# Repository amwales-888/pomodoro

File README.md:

# Pomodoro Timer

This simple project was requested by a client.

### Step 1. Hardware time preset

Produce a Pomodoro Timer where you can set the working time and rest time

The client proposed a set of jumper headers to configure timers along with a sketch of the hardware.

<table>
  <tr>
    <td> </td>
    <td> </td>
  </tr>
</table>

Timers value are hardcoded 

Working time

- 15 minutes
- 30 minutes
- 60 minutes
- 90 minutes

Relax time

-  0 min
-  5 min
- 10 min
- 15 min

A row of LED are used to display the state of the timers.

### Step 2. Start timer

User clicks button to start timer

User hears sound from buzzer

LED progress bar turned on 

- Logic of the LED progress bar
    - Countdown progress bar
        - Ex: 30 minutes timer
        - 10 LEDs are on
        - the last one 10th is flashing
        - Every 3 minutes (time/amount of leds) 1 led turn off, after 3 minutes only 9 are on, the 9th is flashing

### Step 3. Timer is over

Once working timer is over:

- All progress bar LEDs flash
- Buzzer produce sound

Then User click button and Relax(Rest) timer began with the same logic

- Led progress bar has different color
- Once Rest timer finished - another melody is playing

To stop timer the User must hold the button pressed for 3 seconds. 

No pause function needed

### Power requirements

Ideally make it run from a tiny battery like CR2032 or 2-3 AAA Batteries.

### Enclosure requirements

No enclosure or enclosure built from PCB

### Size requirements

Less than 85 mm x 50mm 

## Proposal

 - Use a lowcost <a href="Firmware/pic16f15355/docs/PIC16F-LF-15354-55-Data-Sheet-DS40001853.pdf">pic16lf15355</a> SOIC 28 MCU which can be powered from 1.8v-5v, running from internal oscillator and able to idle at very low current.
 - Use 7 red/green bi-color, low power LEDs 
 - Use 2 AAA Batteries in series at 2v-3v to extend runtime and reduce end user cost over lithium CR2032 cell.
 - Use Microchip MPLAB-X, XC8 and Pickit5 for development.
 - 67mm x 40mm board area, battery holder mounted on the back.

<table>
  <tr>
    <td> </td>
    <td> </td>
  </tr>
</table>

## Completed Project 

Working, partially populated board 

## Project revision

I recently started investigating the py32 series of microcontrollers from puya, these are very low cost ( 12cents, you read that correctly ) arm-cortex-m0 processors running at 24MHz.
I ported the pomodoro firmware for the pic16 targeting the py32 controller and redsigned the board to support a tssop20 package. The new hardware is aimed at owering costs, along with the processor selection I opted for 14 leds in 0603 packages to reduce the cost. The complete BOM comes in at less than $1 and has feature parity with the original, supporting the same number of output and inputs as the original.

<table>
  <tr>
    <td> </td>
    <td> </td>
  </tr>
</table>

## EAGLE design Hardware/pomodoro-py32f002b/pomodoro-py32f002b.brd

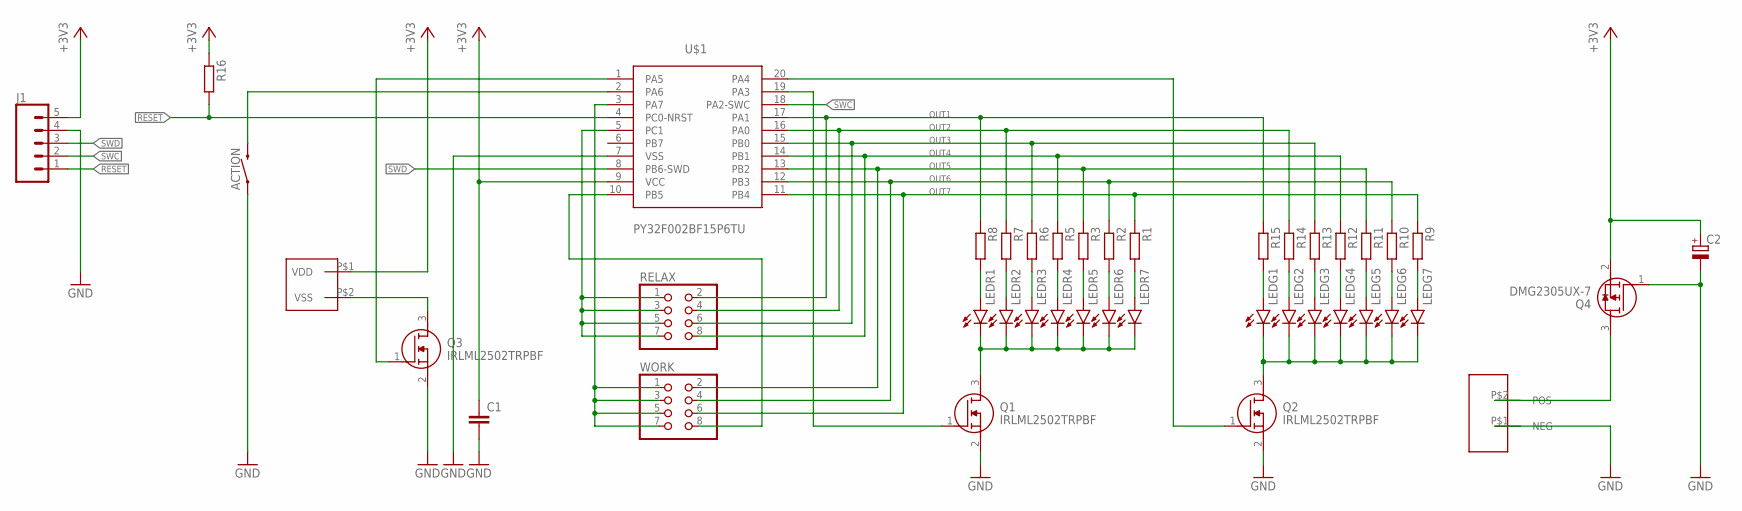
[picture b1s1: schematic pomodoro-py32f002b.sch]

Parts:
ACTION: MOMENTARY-SWITCH-SPST-SMD-6.0X3.5MM; TACTILE_SWITCH_SMD_6.0X3.5MM
C1: C-EUC0805; C0805
C2: CPOL-EUE2.5-5; E2,5-5
J1: CONN_05; 1X05
LEDG1, LEDG2, LEDG3, LEDG4, LEDG5, LEDG6, LEDG7: 20ma; SML0805
LEDR1, LEDR2, LEDR3, LEDR4, LEDR5, LEDR6, LEDR7: 20ma; SML0805
Q1, Q2, Q3: IRLML2502TRPBF; SOT95P237X112-3N
Q4: DMG2305UX-7; SOT96P240X115-3N
R1, R2, R3, R5, R6, R7, R8, R9, R10, R11, R12, R13, R14, R15, R16: 100R; R0805
RELAX: PINHD-2X4; 2X04
U$1: PY32F002BF15P6TU; TSSOP20
U$2: BUZZER8X8
U$3: 2AAABATT; 2AAABATTSER
WORK: PINHD-2X4; 2X04

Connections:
+3V3: C1.1, C2.+, J1.5, Q4.2 (S), R16.1, U$1.9 (VCC), U$2.P$1 (VDD)
BIN: Q1.1 (G), U$1.19 (PA3); also elsewhere on the board
BIN1: Q2.1 (G), U$1.20 (PA4); also elsewhere on the board
GND: ACTION.1, C1.2, C2.-, J1.4, Q1.2 (S), Q2.2 (S), Q3.2 (S), Q4.1 (G), U$1.7 (VSS), U$3.P$1 (NEG); also elsewhere on the board
LEDR1: LEDR1.A, R8.2
unnamed: LEDG7.A, R9.2
unnamed: LEDG6.A, R10.2
unnamed: LEDG5.A, R11.2
unnamed: LEDG4.A, R12.2
unnamed: LEDG3.A, R13.2
unnamed: LEDG2.A, R14.2
unnamed: LEDG1.A, R15.2
unnamed: LEDR7.A, R1.2
unnamed 14: LEDG1.C, LEDG2.C, LEDG3.C, LEDG4.C, LEDG5.C, LEDG6.C, LEDG7.C, Q2.3 (D); also elsewhere on the board
unnamed: LEDR6.A, R2.2
unnamed: LEDR5.A, R3.2
unnamed: LEDR4.A, R5.2
unnamed: LEDR3.A, R6.2
unnamed: LEDR2.A, R7.2
unnamed 21: Q3.3 (D), U$2.P$2 (VSS); also elsewhere on the board
unnamed: ACTION.2, U$1.2 (PA6)
unnamed 24: Q3.1 (G), U$1.1 (PA5); also elsewhere on the board
unnamed: U$1.3 (PA7), WORK.1, WORK.3, WORK.5, WORK.7
unnamed: RELAX.1, RELAX.3, RELAX.5, RELAX.7, U$1.5 (PC1)
unnamed 27: LEDR1.C, LEDR2.C, LEDR3.C, LEDR4.C, LEDR5.C, LEDR6.C, LEDR7.C, Q1.3 (D); also elsewhere on the board
unnamed: Q4.3 (D), U$3.P$2 (POS)
OUT1: R8.1, R15.1, RELAX.2, U$1.17 (PA1)
OUT2: R7.1, R14.1, RELAX.4, U$1.16 (PA0)
OUT3: R6.1, R13.1, RELAX.6, U$1.15 (PB0)
OUT4: R5.1, R12.1, RELAX.8, U$1.14 (PB1)
OUT5: R3.1, R11.1, U$1.13 (PB2), WORK.2
OUT6: R2.1, R10.1, U$1.12 (PB3), WORK.4
OUT7: R1.1, R9.1, U$1.11 (PB4), WORK.6
OUT8: U$1.10 (PB5), WORK.8
RESET: J1.1, R16.2, U$1.4 (PC0-NRST)
SWC: J1.2, U$1.18 (PA2-SWC)
SWD: J1.3, U$1.8 (PB6-SWD)

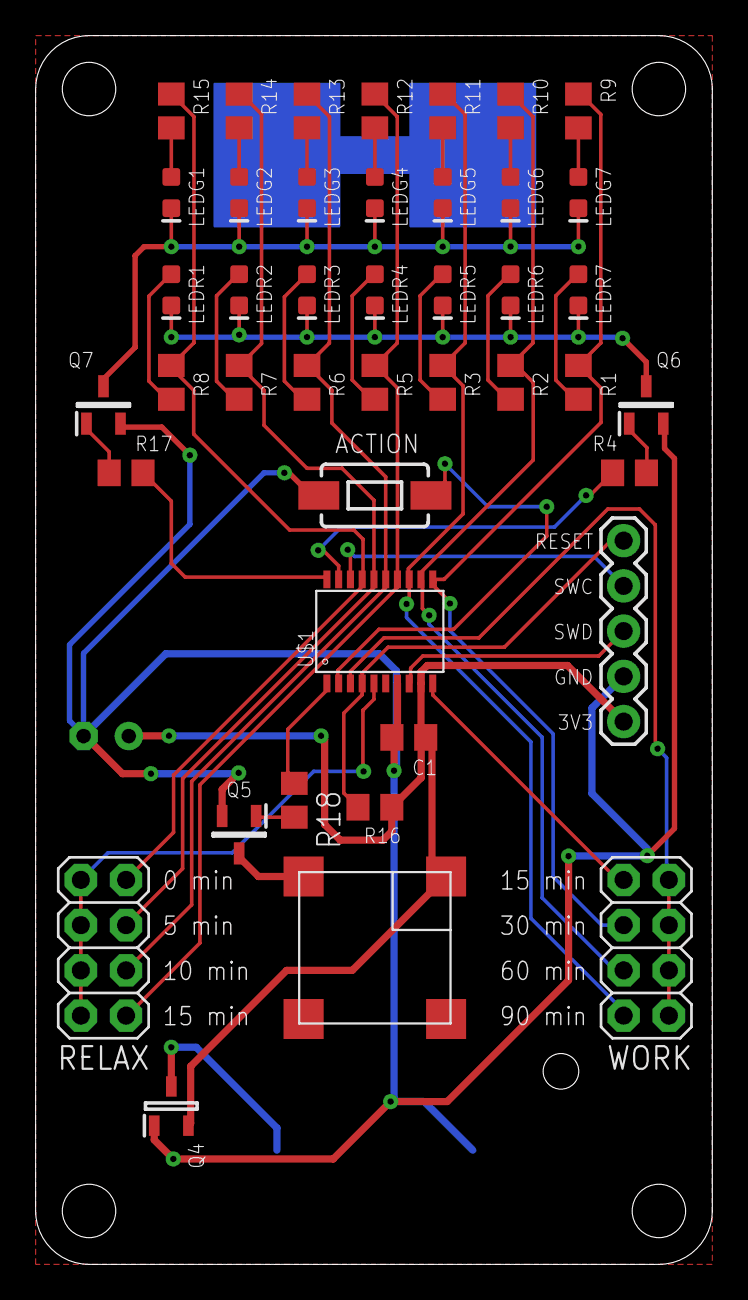
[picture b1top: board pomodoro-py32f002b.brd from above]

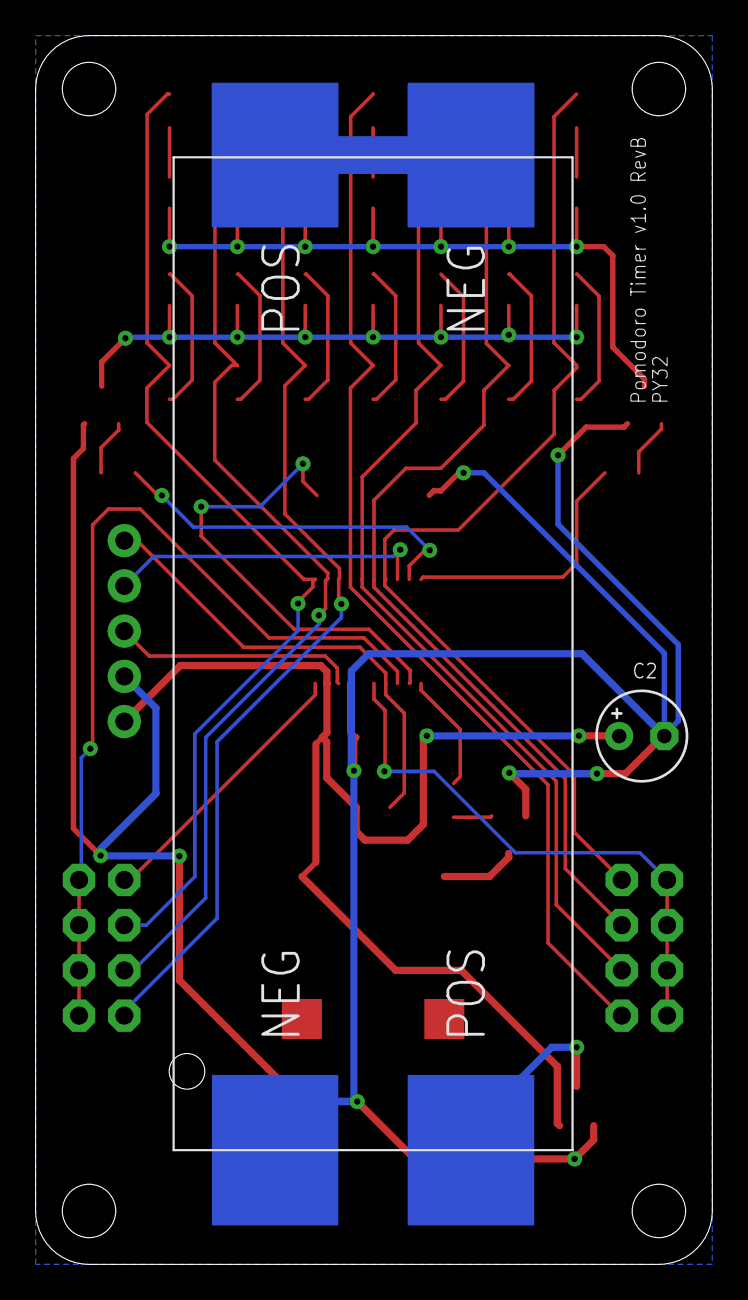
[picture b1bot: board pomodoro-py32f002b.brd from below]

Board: 2 copper layers, 38.0 x 69.0 mm, 45 parts (2 on the bottom side), 40 nets.

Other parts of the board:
Q5, Q6, Q7: MMBT3904LT3G; SOT96P237X111-3N
R4, R18: 10k; R0805
R17: 10K; R0805

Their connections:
BIN: R4.1; also elsewhere on the board
BIN1: R17.1; also elsewhere on the board
GND: Q5.2, Q6.2, Q7.2; also elsewhere on the board
unnamed: Q7.1, R17.2
unnamed 14: Q7.3; also elsewhere on the board
unnamed: Q6.1, R4.2
unnamed 21: Q5.3; also elsewhere on the board
unnamed: Q5.1, R18.2
unnamed 24: R18.1; also elsewhere on the board
unnamed 27: Q6.3; also elsewhere on the board

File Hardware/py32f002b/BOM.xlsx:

|  | LCSC Part Number | Manufacture Part Number | Manufacturer | Customer NO. | Package | Description |  |  | Unit Price($) |  |  | #Required | Price
 |  | C7496820 | F.0603.00139/P2-0603R1TS2-06T-002 | TUOZHAN |  | 603 | 5mA -40â„ƒ~+85â„ƒ Red 120Â° 0603 LED Indication - Discrete ROHS |  |  | 3.0999999999999999E-3 |  |  | 7 | 2.1700000000000001E-2
 |  | C7496818 | F.0603.00025/P2-0603G1TS2-06T-002 | TUOZHAN |  | 603 | 5mA 230mcd 520nm~525nm -40â„ƒ~+85â„ƒ Emerald 120Â° 2.6V~2.9V 0603 LED Indicatio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 |  |  | 2.8999999999999998E-3 |  |  | 7 | 2.0299999999999999E-2
 |  | C94599 | MLT-8530 | Jiangsu Huaneng Elec |  | SMD,8.5x8.5mm | 80dB Externally Driven Magnetic 2.7kHz SMD,8.5x8.5mm Buzzers ROHS |  |  | 0.19239999999999999 |  |  | 1 | 0.19239999999999999
 |  | C22438998 | PY32F002BF15P6TR | PUYAï¼‰ |  | TSSOP-20 | TSSOP-20 Microcontrollers (MCU/MPU/SOC) ROHS |  |  | 0.13689999999999999 |  |  | 1 | 0.13689999999999999
 |  | C5290190 | BH-AAA-B1AJ015-60 | MYOUNG |  | - | Battery case No 7 - Button And Strip Battery Connector ROHS |  |  | 0.27139999999999997 |  |  | 1 | 0.27139999999999997
 |  | C429959 | 12251140CNG0S115001 | JILN |  | Plugin,P=2.54mm | 3A Straight Square Pins 2.5mm 40P 6mm -40â„ƒ~+105â„ƒ 3mm 2.54mm Plugin Black Br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 |  |  | 0.1016 |  |  | 1 | 0.1016
 |  | C17471 | 0805W8F1500T5E | UNI-ROYAL(Uniroyal Elec) |  | 805 | 125mW Thick Film Resistors 150V Â±100ppm/â„ƒ Â±1% 150Î© 0805 Chip Resistor - Su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 |  |  | 1.6999999999999999E-3 |  |  | 14 | 2.3799999999999998E-2
 |  | C150470 | DMG2305UX-7 | Diodes Incorporated |  | SOT-23 | 20V 4.2A 52mÎ©@4.5V,4.2A 1.4W 900mV@250uA 1PCSPChannel SOT-23 MOSFETs ROHS |  |  | 4.6600000000000003E-2 |  |  | 1 | 4.6600000000000003E-2
 |  | C337069 | SL3906 | Slkor(SLKORMICRO Elec.) |  | SOT-23 | 40V 225mW 100@10mA,1V 200mA PNP SOT-23 Bipolar (BJT) ROHS |  |  | 7.4999999999999997E-3 |  |  | 3 | 2.2499999999999999E-2
 |  | C66501 | CL10B104KO8NNNC | Samsung Electro-Mechanics |  | 603 | 16V 100nF X7R Â±10% 0603 Multilayer Ceramic Capacitors MLCC - SMD/SMT ROHS |  |  | 2.5999999999999999E-3 |  |  | 1 | 2.5999999999999999E-3
 |  | C84376 | RC0805FR-0710KL | YAGEO |  | 805 | 125mW Thick Film Resistors 150V Â±100ppm/â„ƒ Â±1% 10kÎ© 0805 Chip Resistor - Su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 |  |  | 1.9E-3 |  |  | 1 | 1.9E-3
 |  | C7499926 | CD110107M1A0407VFL | HRK |  | Plugin,D4xL7mm | 100uF 10V Plugin,D4xL7mm Aluminum Electrolytic Capacitors - Leaded ROHS |  |  | 5.5999999999999999E-3 |  |  | 1 | 5.5999999999999999E-3
 |  |  |  |  |  |  |  |  |  |  |  |  |  | 0.84730000000000005
 |  | ACTION | MOMENTARY-SWITCH-SPST-SMD-6.0X3.5MM | MOMENTARY-SWITCH-SPST-SMD-6.0X3.5MM
 |  | C1 | 100nf | C-EUC0805 |  | CAPACITOR, European symbol
 |  | C2 | 100uf | CPOL-EUE2.5-5 |  | POLARIZED CAPACITOR, European symbol
 |  | J1 |  | CONN_05 |  | PIN HEADER
 |  | LEDG1 | 20ma | LEDSML0805 |  | LED |  | 3.0999999999999999E-3
 |  | LEDG2 | 20ma | LEDSML0805 |  | LED |  | 3.0999999999999999E-3
 |  | LEDG3 | 20ma | LEDSML0805 |  | LED |  | 3.0999999999999999E-3
 |  | LEDG4 | 20ma | LEDSML0805 |  | LED |  | 3.0999999999999999E-3
 |  | LEDG5 | 20ma | LEDSML0805 |  | LED |  | 3.0999999999999999E-3
 |  | LEDG6 | 20ma | LEDSML0805 |  | LED |  | 3.0999999999999999E-3
 |  | LEDG7 | 20ma | LEDSML0805 |  | LED |  | 3.0999999999999999E-3
 |  | LEDR1 | 20ma | LEDSML0805 |  | LED |  | 3.0999999999999999E-3
 |  | LEDR2 | 20ma | LEDSML0805 |  | LED |  | 3.0999999999999999E-3
 |  | LEDR3 | 20ma | LEDSML0805 |  | LED |  | 3.0999999999999999E-3
 |  | LEDR4 | 20ma | LEDSML0805 |  | LED |  | 3.0999999999999999E-3
 |  | LEDR5 | 20ma | LEDSML0805 |  | LED |  | 3.0999999999999999E-3
 |  | LEDR6 | 20ma | LEDSML0805 | C7496820 | LED |  | 3.0999999999999999E-3
 |  | LEDR7 | 20ma | LEDSML0805 | C7496818 | LED |  | 3.0999999999999999E-3
 |  | Q4 | DMG2305UX-7 | DMG2305UX-7 | C150470 | MOSFET P-Ch 20V 5A Enhancement SOT23 Diodes Inc DMG2305UX-7 P-channel MOSFET Tr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 |  | 4.6600000000000003E-2
 |  | Q5 | MMBT3904LT3G | MMBT3904LT3G | C337069 | Transistor NPN 40V 200mA SOT-23 ON Semi MMBT3904LT3G NPN Bipolar Transistor, 90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
 |  | Q6 | MMBT3904LT3G | MMBT3904LT3G | C337069 | Transistor NPN 40V 200mA SOT-23 ON Semi MMBT3904LT3G NPN Bipolar Transistor, 90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
 |  | Q7 | MMBT3904LT3G | MMBT3904LT3G | C337069 | Transistor NPN 40V 200mA SOT-23 ON Semi MMBT3904LT3G NPN Bipolar Transistor, 90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
 |  | R1 | 100R | R-EU_R0805 |  | RESISTOR, European symbol
 |  | R2 | 100R | R-EU_R0805 |  | RESISTOR, European symbol
 |  | R3 | 100R | R-EU_R0805 |  | RESISTOR, European symbol
 |  | R4 | 10k | R-EU_R0805 |  | RESISTOR, European symbol
 |  | R5 | 100R | R-EU_R0805 |  | RESISTOR, European symbol
 |  | R6 | 100R | R-EU_R0805 |  | RESISTOR, European symbol
 |  | R7 | 100R | R-EU_R0805 |  | RESISTOR, European symbol
 |  | R8 | 100R | R-EU_R0805 |  | RESISTOR, European symbol
 |  | R9 | 100R | R-EU_R0805 |  | RESISTOR, European symbol
 |  | R10 | 100R | R-EU_R0805 |  | RESISTOR, European symbol
 |  | R11 | 100R | R-EU_R0805 |  | RESISTOR, European symbol
 |  | R12 | 100R | R-EU_R0805 |  | RESISTOR, European symbol
 |  | R13 | 100R | R-EU_R0805 |  | RESISTOR, European symbol
 |  | R14 | 100R | R-EU_R0805 |  | RESISTOR, European symbol
 |  | R15 | 100R | R-EU_R0805 |  | RESISTOR, European symbol
 |  | R16 | 100R | R-EU_R0805 |  | RESISTOR, European symbol
 |  | R17 | 10K | R-EU_R0805 |  | RESISTOR, European symbol
 |  | R18 | 10k | R-EU_R0805 |  | RESISTOR, European symbol
 |  | RELAX | 3A Straight Square Pins 2.5mm | PINHD-2X4 | C429959 | PIN HEADER
 |  | U$1 | PY32F002BF15P6TU | PY32F002BF15P6TU | C22438998
 |  | U$2 | BUZZER8X8 | BUZZER8X8 | C94599
 |  | U$3 | 2AAABATT | 2AAABATT | C5290190
 |  | WORK | 3A Straight Square Pins 2.5mm | PINHD-2X4 | C429959 | PIN HEADER

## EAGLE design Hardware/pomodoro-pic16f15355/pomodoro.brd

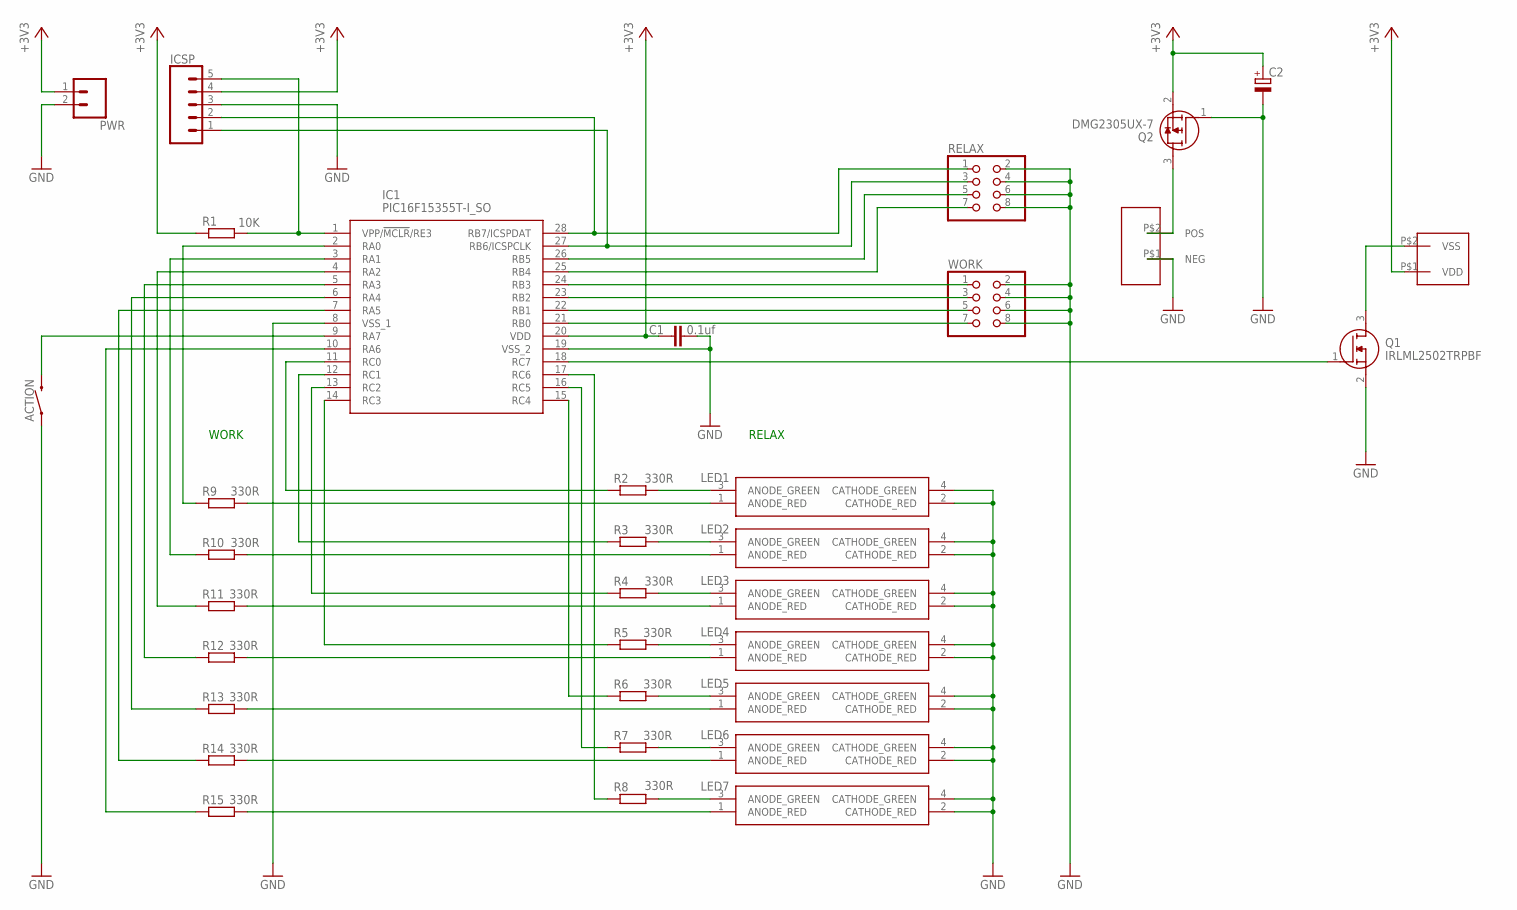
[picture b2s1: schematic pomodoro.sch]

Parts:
ACTION: MOMENTARY-SWITCH-SPST-SMD-6.0X3.5MM; TACTILE_SWITCH_SMD_6.0X3.5MM
C1: 0.1uf; C0805
C2: CPOL-EUE2.5-5; E2,5-5
IC1: PIC16F15355T-I_SO; SOIC127P1030X265-28M
ICSP: CONN_05; 1X05
LED1, LED2, LED3, LED4, LED5, LED6, LED7: APBD3224LSURKCGKC
PWR: CONN_02; 1X02
Q1: IRLML2502TRPBF; SOT95P237X112-3N
Q2: DMG2305UX-7; SOT96P240X115-3N
R1: 10K; R0805
R2, R3, R4, R5, R6, R7, R8, R9, R10, R11, R12, R13, R14, R15: 330R; R0805
RELAX: PINHD-2X4; 2X04
U$1: 2AAABATT; 2AAABATTSER
U$2: BUZZER8X8
WORK: PINHD-2X4; 2X04

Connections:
+3V3: C1.1, C2.+, IC1.20 (VDD), ICSP.4, PWR.1, Q2.2 (S), R1.1, U$2.P$1 (VDD)
GND: ACTION.1, C1.2, C2.-, IC1.8 (VSS_1), IC1.19 (VSS_2), ICSP.3, LED1.2 (CATHODE_RED), LED1.4 (CATHODE_GREEN), LED2.2 (CATHODE_RED), LED2.4 (CATHODE_GREEN), LED3.2 (CATHODE_RED), LED3.4 (CATHODE_GREEN), LED4.2 (CATHODE_RED), LED4.4 (CATHODE_GREEN), LED5.2 (CATHODE_RED), LED5.4 (CATHODE_GREEN), LED6.2 (CATHODE_RED), LED6.4 (CATHODE_GREEN), LED7.2 (CATHODE_RED), LED7.4 (CATHODE_GREEN), PWR.2, Q1.2 (S), Q2.1 (G), RELAX.2, RELAX.4, RELAX.6, RELAX.8, U$1.P$1 (NEG), WORK.2, WORK.4, WORK.6, WORK.8
unnamed: IC1.1 (VPP/!MCLR!/RE3), ICSP.5, R1.2
unnamed: LED1.1 (ANODE_RED), R9.2
unnamed: LED2.1 (ANODE_RED), R10.2
unnamed: IC1.28 (RB7/ICSPDAT), ICSP.2, RELAX.1
unnamed: IC1.27 (RB6/ICSPCLK), ICSP.1, RELAX.3
unnamed: LED3.1 (ANODE_RED), R11.2
unnamed: LED4.1 (ANODE_RED), R12.2
unnamed: LED5.1 (ANODE_RED), R13.2
unnamed: LED6.1 (ANODE_RED), R14.2
unnamed: LED7.1 (ANODE_RED), R15.2
unnamed: LED1.3 (ANODE_GREEN), R2.2
unnamed: LED2.3 (ANODE_GREEN), R3.2
unnamed: LED3.3 (ANODE_GREEN), R4.2
unnamed: LED4.3 (ANODE_GREEN), R5.2
unnamed: LED5.3 (ANODE_GREEN), R6.2
unnamed: LED6.3 (ANODE_GREEN), R7.2
unnamed: LED7.3 (ANODE_GREEN), R8.2
unnamed: ACTION.2, IC1.9 (RA7)
unnamed: IC1.11 (RC0), R2.1
unnamed: IC1.12 (RC1), R3.1
unnamed: IC1.13 (RC2), R4.1
unnamed: IC1.14 (RC3), R5.1
unnamed: IC1.15 (RC4), R6.1
unnamed: IC1.16 (RC5), R7.1
unnamed: IC1.17 (RC6), R8.1
unnamed: IC1.18 (RC7), Q1.1 (G)
unnamed: IC1.21 (RB0), WORK.7
unnamed: IC1.22 (RB1), WORK.5
unnamed: IC1.23 (RB2), WORK.3
unnamed: IC1.24 (RB3), WORK.1
unnamed: IC1.25 (RB4), RELAX.7
unnamed: IC1.26 (RB5), RELAX.5
unnamed: IC1.2 (RA0), R9.1
unnamed: IC1.3 (RA1), R10.1
unnamed: IC1.4 (RA2), R11.1
unnamed: IC1.5 (RA3), R12.1
unnamed: IC1.6 (RA4), R13.1
unnamed: IC1.7 (RA5), R14.1
unnamed: IC1.10 (RA6), R15.1
unnamed: Q1.3 (D), U$2.P$2 (VSS)
unnamed: Q2.3 (D), U$1.P$2 (POS)

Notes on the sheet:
WORK
RELAX

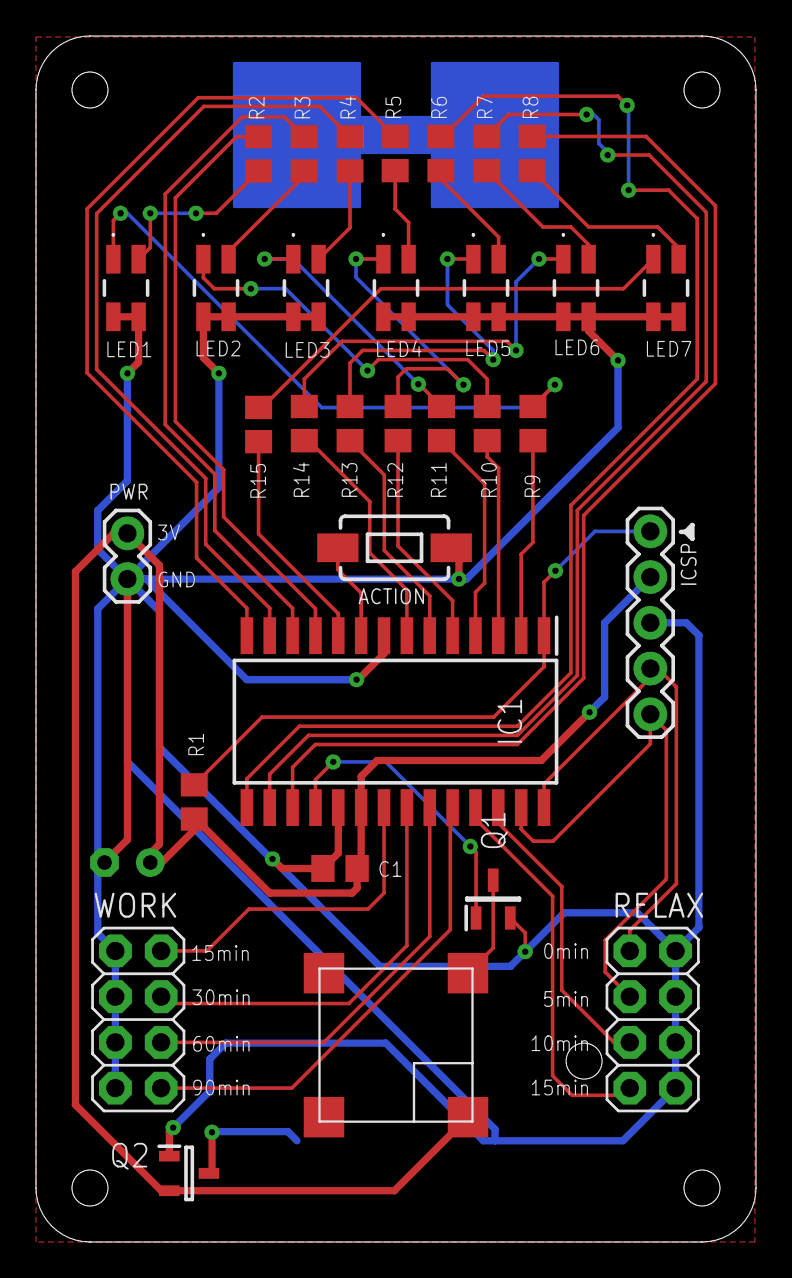
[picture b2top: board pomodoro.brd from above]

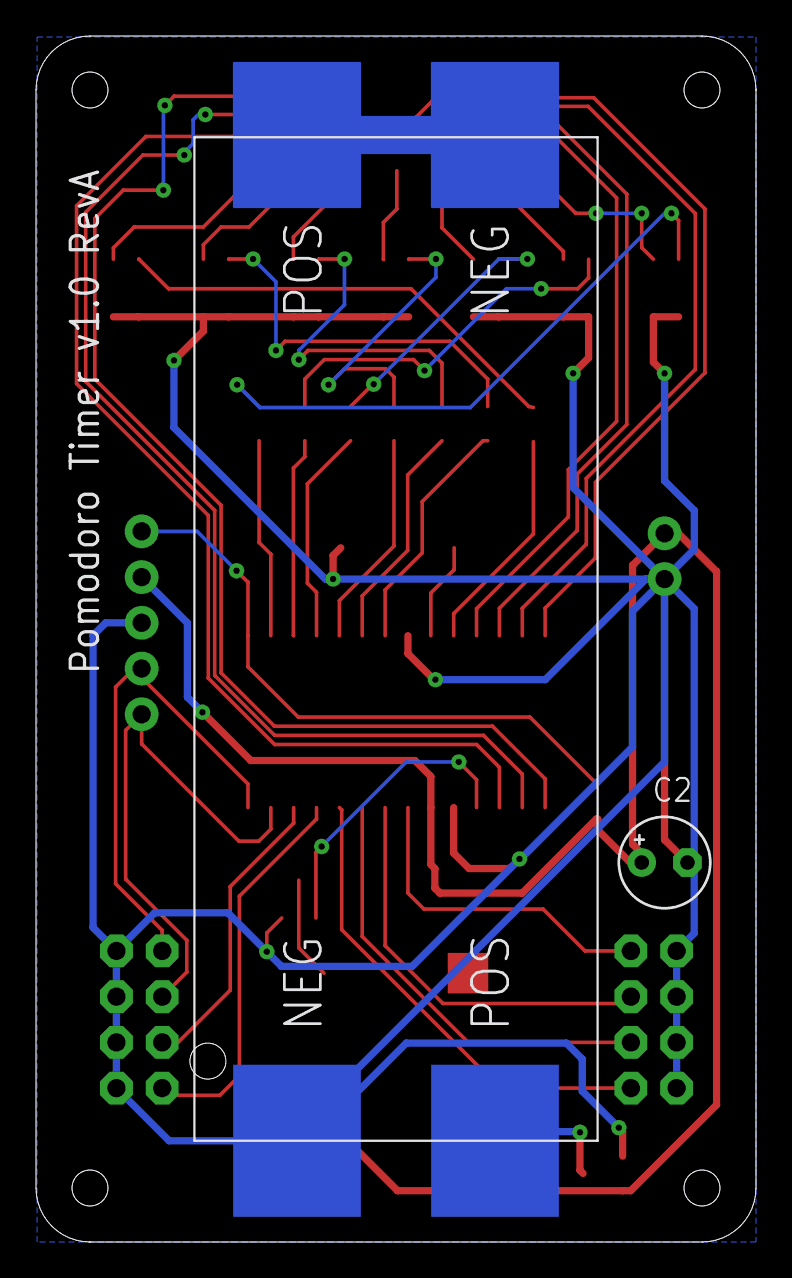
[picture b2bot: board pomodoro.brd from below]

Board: 2 copper layers, 40.0 x 67.0 mm, 34 parts (2 on the bottom side), 43 nets.

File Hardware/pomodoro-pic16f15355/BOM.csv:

"Part";"Value";"Device";"Package";"Description";"DESCRIPTION";"HEIGHT";"MANUFACTURER_NAME";"MANUFACTURER_PART_NUMBER";"MOUSER_PART_NUMBER";"MOUSER_PRICE-STOCK";"POPULARITY";"PROD_ID";"SF_SKU";"SPICEPREFIX";
"ACTION";"MOMENTARY-SWITCH-SPST-SMD-6.0X3.5MM";"MOMENTARY-SWITCH-SPST-SMD-6.0X3.5MM";"TACTILE_SWITCH_SMD_6.0X3.5MM";"Momentary Switch (Pushbutton) - SPST";"";"";"";"";"";"";"";"SWCH-14278";"COM-08229";"";
"C1";"0.1uf";"C-EUC0805";"C0805";"CAPACITOR, European symbol";"";"";"";"";"";"";"88";"";"";"C";
"C2";"";"CPOL-EUE2.5-5";"E2,5-5";"POLARIZED CAPACITOR, European symbol";"";"";"";"";"";"";"16";"";"";"C";
"D1";"CUS10S30,H3F";"CUS10S30,H3F";"1SS357TPH3F";"Schottky Diodes & Rectifiers Single High-speed switching";"Schottky Diodes & Rectifiers Single High-speed switching";"1mm";"Toshiba";"CUS10S30,H3F";"757-CUS10S30H3F";"https://www.mouser.co.uk/ProductDetail/Toshiba/CUS10S30H3F?q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";"";"";"";"";
"IC1";"PIC16F15355T-I_SO";"PIC16F15355T-I_SO";"SOIC127P1030X265-28M";"MCU 8-bit PIC RISC 14KB Flash 3.3V/5V 28-Pin SOIC W T/R";"MCU 8-bit PIC RISC 14KB Flash 3.3V/5V 28-Pin SOIC W T/R";"2.65mm";"Microchip";"PIC16F15355T-I/SO";"579-PIC16F15355TI/SO";"https://www.mouser.co.uk/ProductDetail/Microchip-Technology/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";"";"";"";"";
"ICSP";"";"CONN_05";"1X05";"Multi connection point. Often used as Generic Header-pin footprint for 0.1 inch spaced/style header connections";"";"";"";"";"";"";"";"";"";"";
"LED1";"APBD3224LSURKCGKC";"APBD3224LSURKCGKC";"APBD3224LSURKCGKC";"Standard LEDs - SMD 3.2x2.4MM LOW CU RED/GREEN SMD";"Standard LEDs - SMD 3.2x2.4MM LOW CU RED/GREEN SMD";"2.4mm";"Kingbright";"APBD3224LSURKCGKC";"604-APBD3224LSURKCGK";"https://www.mouser.co.uk/ProductDetail/Kingbright/APBD3224LS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";"";"";"";"";
"LED2";"APBD3224LSURKCGKC";"APBD3224LSURKCGKC";"APBD3224LSURKCGKC";"Standard LEDs - SMD 3.2x2.4MM LOW CU RED/GREEN SMD";"Standard LEDs - SMD 3.2x2.4MM LOW CU RED/GREEN SMD";"2.4mm";"Kingbright";"APBD3224LSURKCGKC";"604-APBD3224LSURKCGK";"https://www.mouser.co.uk/ProductDetail/Kingbright/APBD3224LS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";"";"";"";"";
"LED3";"APBD3224LSURKCGKC";"APBD3224LSURKCGKC";"APBD3224LSURKCGKC";"Standard LEDs - SMD 3.2x2.4MM LOW CU RED/GREEN SMD";"Standard LEDs - SMD 3.2x2.4MM LOW CU RED/GREEN SMD";"2.4mm";"Kingbright";"APBD3224LSURKCGKC";"604-APBD3224LSURKCGK";"https://www.mouser.co.uk/ProductDetail/Kingbright/APBD3224LS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";"";"";"";"";
"LED4";"APBD3224LSURKCGKC";"APBD3224LSURKCGKC";"APBD3224LSURKCGKC";"Standard LEDs - SMD 3.2x2.4MM LOW CU RED/GREEN SMD";"Standard LEDs - SMD 3.2x2.4MM LOW CU RED/GREEN SMD";"2.4mm";"Kingbright";"APBD3224LSURKCGKC";"604-APBD3224LSURKCGK";"https://www.mouser.co.uk/ProductDetail/Kingbright/APBD3224LS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";"";"";"";"";
"LED5";"APBD3224LSURKCGKC";"APBD3224LSURKCGKC";"APBD3224LSURKCGKC";"Standard LEDs - SMD 3.2x2.4MM LOW CU RED/GREEN SMD";"Standard LEDs - SMD 3.2x2.4MM LOW CU RED/GREEN SMD";"2.4mm";"Kingbright";"APBD3224LSURKCGKC";"604-APBD3224LSURKCGK";"https://www.mouser.co.uk/ProductDetail/Kingbright/APBD3224LS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";"";"";"";"";
"LED6";"APBD3224LSURKCGKC";"APBD3224LSURKCGKC";"APBD3224LSURKCGKC";"Standard LEDs - SMD 3.2x2.4MM LOW CU RED/GREEN SMD";"Standard LEDs - SMD 3.2x2.4MM LOW CU RED/GREEN SMD";"2.4mm";"Kingbright";"APBD3224LSURKCGKC";"604-APBD3224LSURKCGK";"https://www.mouser.co.uk/ProductDetail/Kingbright/APBD3224LS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";"";"";"";"";
"LED7";"APBD3224LSURKCGKC";"APBD3224LSURKCGKC";"APBD3224LSURKCGKC";"Standard LEDs - SMD 3.2x2.4MM LOW CU RED/GREEN SMD";"Standard LEDs - SMD 3.2x2.4MM LOW CU RED/GREEN SMD";"2.4mm";"Kingbright";"APBD3224LSURKCGKC";"604-APBD3224LSURKCGK";"https://www.mouser.co.uk/ProductDetail/Kingbright/APBD3224LS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";"";"";"";"";
"PWR";"";"CONN_02";"1X02";"Multi connection point. Often used as Generic Header-pin footprint for 0.1 inch spaced/style header connections";"";"";"";"";"";"";"";"";"";"";
"R1";"10K";"R-EU_R0805";"R0805";"RESISTOR, European symbol";"";"";"";"";"";"";"86";"";"";"R";
"R2";"330R";"R-EU_R0805";"R0805";"RESISTOR, European symbol";"";"";"";"";"";"";"86";"";"";"R";
"R3";"330R";"R-EU_R0805";"R0805";"RESISTOR, European symbol";"";"";"";"";"";"";"86";"";"";"R";
"R4";"330R";"R-EU_R0805";"R0805";"RESISTOR, European symbol";"";"";"";"";"";"";"86";"";"";"R";
"R5";"330R";"R-EU_R0805";"R0805";"RESISTOR, European symbol";"";"";"";"";"";"";"86";"";"";"R";
"R6";"330R";"R-EU_R0805";"R0805";"RESISTOR, European symbol";"";"";"";"";"";"";"86";"";"";"R";
"R7";"330R";"R-EU_R0805";"R0805";"RESISTOR, European symbol";"";"";"";"";"";"";"86";"";"";"R";
"R8";"330R";"R-EU_R0805";"R0805";"RESISTOR, European symbol";"";"";"";"";"";"";"86";"";"";"R";
"R9";"330R";"R-EU_R0805";"R0805";"RESISTOR, European symbol";"";"";"";"";"";"";"86";"";"";"R";
"R10";"330R";"R-EU_R0805";"R0805";"RESISTOR, European symbol";"";"";"";"";"";"";"86";"";"";"R";
"R11";"330R";"R-EU_R0805";"R0805";"RESISTOR, European symbol";"";"";"";"";"";"";"86";"";"";"R";
"R12";"330R";"R-EU_R0805";"R0805";"RESISTOR, European symbol";"";"";"";"";"";"";"86";"";"";"R";
"R13";"330R";"R-EU_R0805";"R0805";"RESISTOR, European symbol";"";"";"";"";"";"";"86";"";"";"R";
"R14";"330R";"R-EU_R0805";"R0805";"RESISTOR, European symbol";"";"";"";"";"";"";"86";"";"";"R";
"R15";"330R";"R-EU_R0805";"R0805";"RESISTOR, European symbol";"";"";"";"";"";"";"86";"";"";"R";
"RELAX";"";"PINHD-2X4";"2X04";"PIN HEADER";"";"";"";"";"";"";"47";"";"";"";
"U$1";"2AAABATT";"2AAABATT";"2AAABATTSER";"";"";"";"";"";"";"";"";"";"";"";
"U$2";"BUZZER8X8";"BUZZER8X8";"BUZZER8X8";"";"";"";"";"";"";"";"";"";"";"";
"WORK";"";"PINHD-2X4";"2X04";"PIN HEADER";"";"";"";"";"";"";"47";"";"";"";

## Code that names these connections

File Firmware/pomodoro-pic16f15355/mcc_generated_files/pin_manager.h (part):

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// get/set IO_LEDR0 aliases
#define IO_LEDR0_TRIS                 TRISAbits.TRISA0
#define IO_LEDR0_LAT                  LATAbits.LATA0
#define IO_LEDR0_PORT                 PORTAbits.RA0
#define IO_LEDR0_WPU                  WPUAbits.WPUA0
#define IO_LEDR0_OD                   ODCONAbits.ODCA0
#define IO_LEDR0_ANS                  ANSELAbits.ANSA0
#define IO_LEDR0_SetHigh()            do { LATAbits.LATA0 = 1; } while(0)
#define IO_LEDR0_SetLow()             do { LATAbits.LATA0 = 0; } while(0)
#define IO_LEDR0_Toggle()             do { LATAbits.LATA0 = ~LATAbits.LATA0; } while(0)
#define IO_LEDR0_GetValue()           PORTAbits.RA0
#define IO_LEDR0_SetDigitalInput()    do { TRISAbits.TRISA0 = 1; } while(0)
#define IO_LEDR0_SetDigitalOutput()   do { TRISAbits.TRISA0 = 0; } while(0)
#define IO_LEDR0_SetPullup()          do { WPUAbits.WPUA0 = 1; } while(0)
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// get/set IO_LEDR1 aliases
#define IO_LEDR1_TRIS                 TRISAbits.TRISA1
#define IO_LEDR1_LAT                  LATAbits.LATA1
#define IO_LEDR1_PORT                 PORTAbits.RA1
#define IO_LEDR1_WPU                  WPUAbits.WPUA1
#define IO_LEDR1_OD                   ODCONAbits.ODCA1
#define IO_LEDR1_ANS                  ANSELAbits.ANSA1
#define IO_LEDR1_SetHigh()            do { LATAbits.LATA1 = 1; } while(0)
#define IO_LEDR1_SetLow()             do { LATAbits.LATA1 = 0; } while(0)
#define IO_LEDR1_Toggle()             do { LATAbits.LATA1 = ~LATAbits.LATA1; } while(0)
#define IO_LEDR1_GetValue()           PORTAbits.RA1
#define IO_LEDR1_SetDigitalInput()    do { TRISAbits.TRISA1 = 1; } while(0)
#define IO_LEDR1_SetDigitalOutput()   do { TRISAbits.TRISA1 = 0; } while(0)
#define IO_LEDR1_SetPullup()          do { WPUAbits.WPUA1 = 1; } while(0)
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// get/set IO_LEDR2 aliases
#define IO_LEDR2_TRIS                 TRISAbits.TRISA2
#define IO_LEDR2_LAT                  LATAbits.LATA2
#define IO_LEDR2_PORT                 PORTAbits.RA2
#define IO_LEDR2_WPU                  WPUAbits.WPUA2
#define IO_LEDR2_OD                   ODCONAbits.ODCA2
#define IO_LEDR2_ANS                  ANSELAbits.ANSA2
#define IO_LEDR2_SetHigh()            do { LATAbits.LATA2 = 1; } while(0)
#define IO_LEDR2_SetLow()             do { LATAbits.LATA2 = 0; } while(0)
#define IO_LEDR2_Toggle()             do { LATAbits.LATA2 = ~LATAbits.LATA2; } while(0)
#define IO_LEDR2_GetValue()           PORTAbits.RA2
#define IO_LEDR2_SetDigitalInput()    do { TRISAbits.TRISA2 = 1; } while(0)
#define IO_LEDR2_SetDigitalOutput()   do { TRISAbits.TRISA2 = 0; } while(0)
#define IO_LEDR2_SetPullup()          do { WPUAbits.WPUA2 = 1; } while(0)
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// get/set IO_LEDR3 aliases
#define IO_LEDR3_TRIS                 TRISAbits.TRISA3
#define IO_LEDR3_LAT                  LATAbits.LATA3
#define IO_LEDR3_PORT                 PORTAbits.RA3
#define IO_LEDR3_WPU                  WPUAbits.WPUA3
#define IO_LEDR3_OD                   ODCONAbits.ODCA3
#define IO_LEDR3_ANS                  ANSELAbits.ANSA3
#define IO_LEDR3_SetHigh()            do { LATAbits.LATA3 = 1; } while(0)
#define IO_LEDR3_SetLow()             do { LATAbits.LATA3 = 0; } while(0)
#define IO_LEDR3_Toggle()             do { LATAbits.LATA3 = ~LATAbits.LATA3; } while(0)
#define IO_LEDR3_GetValue()           PORTAbits.RA3
#define IO_LEDR3_SetDigitalInput()    do { TRISAbits.TRISA3 = 1; } while(0)
#define IO_LEDR3_SetDigitalOutput()   do { TRISAbits.TRISA3 = 0; } while(0)
#define IO_LEDR3_SetPullup()          do { WPUAbits.WPUA3 = 1; } while(0)
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// get/set IO_LEDR4 aliases
#define IO_LEDR4_TRIS                 TRISAbits.TRISA4
#define IO_LEDR4_LAT                  LATAbits.LATA4
#define IO_LEDR4_PORT                 PORTAbits.RA4
#define IO_LEDR4_WPU                  WPUAbits.WPUA4
#define IO_LEDR4_OD                   ODCONAbits.ODCA4
#define IO_LEDR4_ANS                  ANSELAbits.ANSA4
#define IO_LEDR4_SetHigh()            do { LATAbits.LATA4 = 1; } while(0)
#define IO_LEDR4_SetLow()             do { LATAbits.LATA4 = 0; } while(0)
#define IO_LEDR4_Toggle()             do { LATAbits.LATA4 = ~LATAbits.LATA4; } while(0)
#define IO_LEDR4_GetValue()           PORTAbits.RA4
#define IO_LEDR4_SetDigitalInput()    do { TRISAbits.TRISA4 = 1; } while(0)
#define IO_LEDR4_SetDigitalOutput()   do { TRISAbits.TRISA4 = 0; } while(0)
#define IO_LEDR4_SetPullup()          do { WPUAbits.WPUA4 = 1; } while(0)
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// get/set IO_LEDR5 aliases
#define IO_LEDR5_TRIS                 TRISAbits.TRISA5
#define IO_LEDR5_LAT                  LATAbits.LATA5
#define IO_LEDR5_PORT                 PORTAbits.RA5
#define IO_LEDR5_WPU                  WPUAbits.WPUA5
#define IO_LEDR5_OD                   ODCONAbits.ODCA5
#define IO_LEDR5_ANS                  ANSELAbits.ANSA5
#define IO_LEDR5_SetHigh()            do { LATAbits.LATA5 = 1; } while(0)
#define IO_LEDR5_SetLow()             do { LATAbits.LATA5 = 0; } while(0)
#define IO_LEDR5_Toggle()             do { LATAbits.LATA5 = ~LATAbits.LATA5; } while(0)
#define IO_LEDR5_GetValue()           PORTAbits.RA5
#define IO_LEDR5_SetDigitalInput()    do { TRISAbits.TRISA5 = 1; } while(0)
#define IO_LEDR5_SetDigitalOutput()   do { TRISAbits.TRISA5 = 0; } while(0)
#define IO_LEDR5_SetPullup()          do { WPUAbits.WPUA5 = 1; } while(0)
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// get/set IO_LEDR6 aliases
#define IO_LEDR6_TRIS                 TRISAbits.TRISA6
#define IO_LEDR6_LAT                  LATAbits.LATA6
#define IO_LEDR6_PORT                 PORTAbits.RA6
#define IO_LEDR6_WPU                  WPUAbits.WPUA6
#define IO_LEDR6_OD                   ODCONAbits.ODCA6
#define IO_LEDR6_ANS                  ANSELAbits.ANSA6
#define IO_LEDR6_SetHigh()            do { LATAbits.LATA6 = 1; } while(0)
#define IO_LEDR6_SetLow()             do { LATAbits.LATA6 = 0; } while(0)
#define IO_LEDR6_Toggle()             do { LATAbits.LATA6 = ~LATAbits.LATA6; } while(0)
#define IO_LEDR6_GetValue()           PORTAbits.RA6
#define IO_LEDR6_SetDigitalInput()    do { TRISAbits.TRISA6 = 1; } while(0)
#define IO_LEDR6_SetDigitalOutput()   do { TRISAbits.TRISA6 = 0; } while(0)
#define IO_LEDR6_SetPullup()          do { WPUAbits.WPUA6 = 1; } while(0)
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// get/set IO_BUTTON aliases
#define IO_BUTTON_TRIS                 TRISAbits.TRISA7
#define IO_BUTTON_LAT                  LATAbits.LATA7
#define IO_BUTTON_PORT                 PORTAbits.RA7
#define IO_BUTTON_WPU                  WPUAbits.WPUA7
#define IO_BUTTON_OD                   ODCONAbits.ODCA7
#define IO_BUTTON_ANS                  ANSELAbits.ANSA7
#define IO_BUTTON_SetHigh()            do { LATAbits.LATA7 = 1; } while(0)
#define IO_BUTTON_SetLow()             do { LATAbits.LATA7 = 0; } while(0)
#define IO_BUTTON_Toggle()             do { LATAbits.LATA7 = ~LATAbits.LATA7; } while(0)
#define IO_BUTTON_GetValue()           PORTAbits.RA7
#define IO_BUTTON_SetDigitalInput()    do { TRISAbits.TRISA7 = 1; } while(0)
#define IO_BUTTON_SetDigitalOutput()   do { TRISAbits.TRISA7 = 0; } while(0)
#define IO_BUTTON_SetPullup()          do { WPUAbits.WPUA7 = 1; } while(0)
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// get/set IO_WORK0 aliases
#define IO_WORK0_TRIS                 TRISBbits.TRISB0
#define IO_WORK0_LAT                  LATBbits.LATB0
#define IO_WORK0_PORT                 PORTBbits.RB0
#define IO_WORK0_WPU                  WPUBbits.WPUB0
#define IO_WORK0_OD                   ODCONBbits.ODCB0
#define IO_WORK0_ANS                  ANSELBbits.ANSB0
#define IO_WORK0_SetHigh()            do { LATBbits.LATB0 = 1; } while(0)
#define IO_WORK0_SetLow()             do { LATBbits.LATB0 = 0; } while(0)
#define IO_WORK0_Toggle()             do { LATBbits.LATB0 = ~LATBbits.LATB0; } while(0)
#define IO_WORK0_GetValue()           PORTBbits.RB0
#define IO_WORK0_SetDigitalInput()    do { TRISBbits.TRISB0 = 1; } while(0)
#define IO_WORK0_SetDigitalOutput()   do { TRISBbits.TRISB0 = 0; } while(0)
#define IO_WORK0_SetPullup()          do { WPUBbits.WPUB0 = 1; } while(0)
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// get/set IO_WORK1 aliases
#define IO_WORK1_TRIS                 TRISBbits.TRISB1
#define IO_WORK1_LAT                  LATBbits.LATB1
#define IO_WORK1_PORT                 PORTBbits.RB1
#define IO_WORK1_WPU                  WPUBbits.WPUB1
#define IO_WORK1_OD                   ODCONBbits.ODCB1
#define IO_WORK1_ANS                  ANSELBbits.ANSB1
#define IO_WORK1_SetHigh()            do { LATBbits.LATB1 = 1; } while(0)
#define IO_WORK1_SetLow()             do { LATBbits.LATB1 = 0; } while(0)
#define IO_WORK1_Toggle()             do { LATBbits.LATB1 = ~LATBbits.LATB1; } while(0)
#define IO_WORK1_GetValue()           PORTBbits.RB1
#define IO_WORK1_SetDigitalInput()    do { TRISBbits.TRISB1 = 1; } while(0)
#define IO_WORK1_SetDigitalOutput()   do { TRISBbits.TRISB1 = 0; } while(0)
#define IO_WORK1_SetPullup()          do { WPUBbits.WPUB1 = 1; } while(0)
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// get/set IO_WORK2 aliases
#define IO_WORK2_TRIS                 TRISBbits.TRISB2
#define IO_WORK2_LAT                  LATBbits.LATB2
#define IO_WORK2_PORT                 PORTBbits.RB2
#define IO_WORK2_WPU                  WPUBbits.WPUB2
#define IO_WORK2_OD                   ODCONBbits.ODCB2
#define IO_WORK2_ANS                  ANSELBbits.ANSB2
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
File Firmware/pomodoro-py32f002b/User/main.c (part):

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	
	/*
	
	Output PA1 - OUT1 - LEDR1, LEDG1
	Output PA0 - OUT2 - LEDR2, LEDG2
	Output PB0 - OUT3 - LEDR3, LEDG3
	Output PB1 - OUT4 - LEDR4, LEDG4
	Output PB2 - OUT5 - LEDR5, LEDG5
	Output PB3 - OUT6 - LEDR6, LEDG6
	Output PB4 - OUT7 - LEDR7, LEDG7
	Output PB5 - OUT8
	
	
	
	Input PA3 - Enable RED LEDs
	Input PA4 - Enable GREEN LEDs
	Input PA6 - Button

	Output PA5 - Buzzer
	
	*/
	
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	LL_GPIO_SetPinMode(GPIOA, LL_GPIO_PIN_6, LL_GPIO_MODE_INPUT);	

    /* Register interrupt handler for Butto so we can wake from sleep */
    /* Configure PA6 as the EXTI6 interrupt input */
    LL_EXTI_SetEXTISource(LL_EXTI_CONFIG_PORTA, LL_EXTI_CONFIG_LINE6);

    /* Enable EXTI6 */
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
static void PWMConfigure(void)
{
	// PA5 is PWM output TIM1_CH1 its initial state is 
	// configured as a simple output pulled low
	
  LL_TIM_OC_InitTypeDef TIM_OC_Initstruct = {0};
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
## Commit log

2024-05-25 Project checkin
    Project checkin after repository creation
2024-05-25 Added hardware BOM, gerbers and images
2024-05-26 Update README.md
    Added pictures
2024-05-26 Update README.md
    Spelling correction
2024-05-27 Added docs, images and cad libraries
2024-05-27 Update README.md
    Added documentation references and images
2024-05-27 Work on sleep
    Add interrupt on change to button, add button logic to sleep and wakup
2024-05-27 Disable unecessary tasks during sleep
2024-05-27 Filter any button press at startup from sleep
2024-05-30 Switched out diode and added pchannel mosfet, rounded corners, generated new gergbers
2024-06-01 Checked nets Added 3dmodels, moved buzzer to centre and replaced 2mm holes with 3.2mm generated images and gerbers
2024-06-01 Updated BOM and Added docs for mosfets
2024-06-03 Invert LEDs, fix incorrect comments and make time delay more human readable
2024-06-03 Added gerbers to zip file to uploads to manufacturer
2024-06-04 Change order that LEDs countdown, ensure we clear old LEDs
2024-06-04 Changed buzzer ouput to PWM with 2.5KHz freq and 50% duty cycle
2024-06-04 Start and Stop Buzzer in sycn with flashing LEDs
2024-06-08 Added ability to play simple melody while system is running - next we need to start and stop it when appropriate
2024-06-12 Added duration for notes in melody, we now start melody on blink leds and do not loop the melody, it plays once on blink start
2024-06-14 Added default for work and relax if jumpers not connected
2024-06-25 Populated Board
2024-08-04 initial checkin py32 board
2024-08-04 Firmware for py32 checkin
2024-08-08 added pwm to play melody
2024-08-09 Cleanup and play melody support
2024-08-09 Better method to enable and disable pwm
2024-08-11 Using vscode and keil assistant
2024-08-12 Added code to enter deepsleep when button held for 3 seconds
2024-08-15 Reduce current on sleep by disabling outputs, updated hardware, rounded corners, changed leds from 0805 to 0603
2024-09-01 Rename project and directories
    Rename project and directories to better reflect the fact that there are now 2 different hardware/firmware versions ( pic16f15354 and py32f002b )
2024-09-01 Generate gerbers for production
2024-09-01 Update README.md
    Added images

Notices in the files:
Firmware/pomodoro-pic16f15355/mcc_generated_files/pin_manager.h:
(c) 2018 Microchip Technology Inc. and its subsidiaries.
Firmware/pomodoro-py32f002b/User/main.c:
© Copyright (c) Puya Semiconductor Co.
All rights reserved.
© Copyright (c) 2016 STMicroelectronics.
This software component is licensed by ST under BSD 3-Clause license,
the "License"; You may not use this file except in compliance with the
License. You may obtain a copy of the License at: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
(C) COPYRIGHT Puya *****END OF FILE
